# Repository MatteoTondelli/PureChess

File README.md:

# Pure Chess

## Overview
An Arduino-based chessboard that can interact with a _PureData_ patch.

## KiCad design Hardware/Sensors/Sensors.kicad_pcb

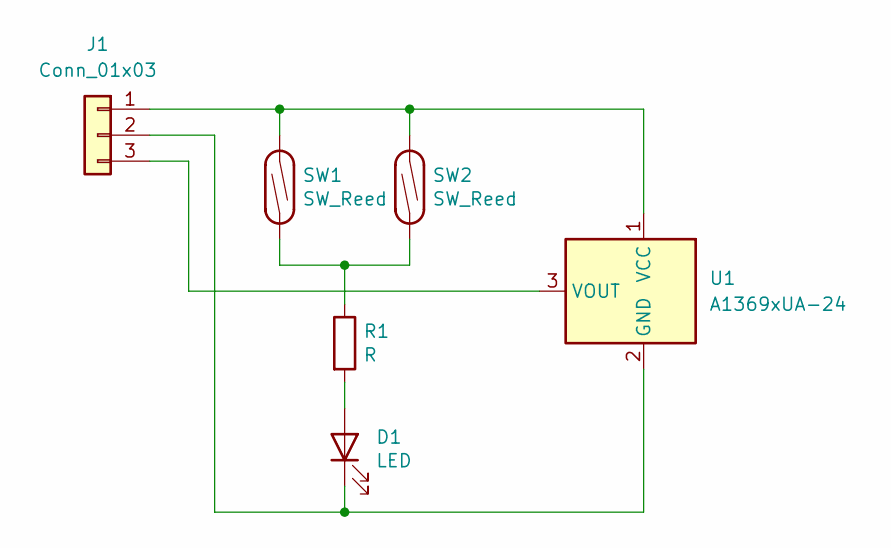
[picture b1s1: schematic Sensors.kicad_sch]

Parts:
D1: LED; LED_0805_2012Metric
J1: Conn_01x03; Pad_03x01
R1: R; R_0805_2012Metric
SW1, SW2: SW_Reed; ReedSwitch 2x14
U1: A1369xUA-24; SOT-23

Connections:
unnamed: D1.1 (K), J1.2, U1.2 (GND)
unnamed: D1.2 (A), R1.2
unnamed: J1.3, U1.3 (VOUT)
unnamed: R1.1, SW1.2, SW2.2
unnamed: J1.1, SW1.1, SW2.1, U1.1 (VCC)

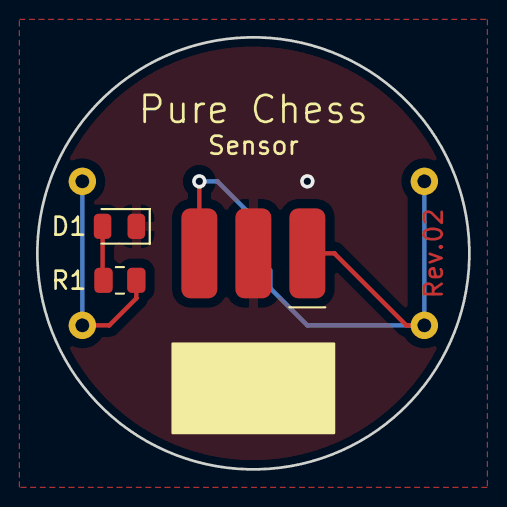
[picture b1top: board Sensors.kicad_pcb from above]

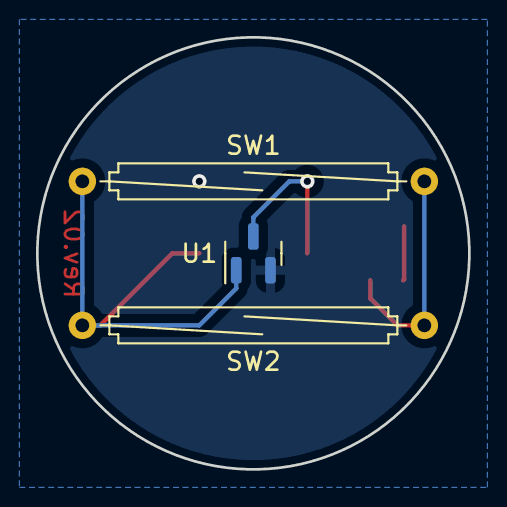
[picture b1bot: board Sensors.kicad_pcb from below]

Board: 2 copper layers, 24.0 x 24.0 mm, 6 parts (3 on the bottom side), 5 nets.

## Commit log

2022-02-06 Started Python development.
2022-02-06 Improved move detection algorithm.
    - Arduino must send all the changes of the board, not only the final position.
2022-02-12 Working on GUI.
    - Created main window with chess board rendering.
    - Started adding some features (Arduino simulation, load game).
2022-02-12 Minor changes.
    - Moved import statement to "__main__" routine.
2022-02-12 Added image for documentation.
2022-03-18 First MIDI interaction between chessboard and PureData.
    - Added "MIDI" and "PatchElements" modules.
    - Improved MIDI output device selection.
    - Added mechanism to send MIDI when a new chess move occurs.
2022-04-08 First working patch.
2022-04-16 Added "Sensors" schematic and PCB layout.
2022-04-21 Sensors Rev.01 sent to production.
    - Generated gerbers for Sensors PCB Rev.01.
2022-09-03 New PCB.
    - Added hall effect sensor.
    - Increased distance for reed switch mount holes.
    - Cables for connections will be soldered on pads instead of PTH.
2022-11-12 Created SerialCommunication.py
    - Created module to handle serial communication with Arduino.
2022-11-12 Updated .gitignore
    - Added "__pycache__" to excluded folder.
2022-11-12 Updated .gitingore
    - Excluded Sphinx "_build" folder.
2022-11-12 Starting documentation.
    - First draft of the project documentation with Sphinx.
2022-11-12 Minor changes on Python code.
    - Improved menu nesting in GUI.
    - Added some docstrings.
2022-11-12 Updated .gitignore
2022-11-12 Updated documentation.
    - Added sensor board information.
    - Fixed few typos.
2022-11-13 Updated documentation.
    - Reorganized all the document tree.
    - Added new stuff.
2022-11-19 Updated documentation.
    - Enhanced "getting started" section.
